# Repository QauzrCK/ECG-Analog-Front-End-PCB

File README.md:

# ECG-Analog-Front-End-PCB

# Low-Noise ECG Biopotential Analog Front-End (AFE)

A single-supply ($3.3\text{ V}$) analog front-end designed to extract, filter, and amplify $1\text{ mV}_{\text{pp}}$ electrocardiography (ECG) signals for microcontroller ADC acquisition, verified in **LTspice** and laid out as a 2-layer PCB in **KiCad**.

## System Specifications & Simulated Performance
* **Supply Voltage:** $3.3\text{ V}$ single-supply ($V_{\text{ref}} = 1.65\text{ V}$ mid-rail bias)
* **Mid-Band Gain:** $530.9\text{ V/V}$ ($54.5\text{ dB}$)
* **Passband Bandwidth:** $3.39\text{ Hz} – 148.7\text{ Hz}$
* **Mains Interference Rejection:** $>35\text{ dB}$ attenuation at $50\text{ Hz}$
* **Input-Referred Noise:** $<10\ \mu\text{V}_{\text{rms}}$ ($0.5–150\text{ Hz}$)

## Signal Chain Architecture
1. **Instrumentation Amplifier (`AD8226`):** Differential gain set to $G_1 = 1 + \frac{49.4\text{ k}\Omega}{5.6\text{ k}\Omega} = 9.82\text{ V/V}$, level-shifted to $V_{\text{ref}} = 1.65\text{ V}$ to prevent clipping from $\pm 150\text{ mV}$ electrode DC offsets.
2. **1st-Order High-Pass Filter:** $C_1 = 10\ \mu\text{F}$ and $R_2 = 4.7\text{ k}\Omega$ ($f_c = 3.39\text{ Hz}$) referenced to $V_{\text{ref}}$ to eliminate respiratory baseline wander while maintaining low source impedance into the notch stage.
3. **Active Twin-T $50\text{ Hz}$ Notch Filter (`LT1490`):** Symmetrical R-R-C / C-C-R bridge ($R = 31.6\text{ k}\Omega$, $C = 100\text{ nF}$, $f_0 = 50.37\text{ Hz}$) with unity-gain output bootstrapping to narrow the notch bandwidth and preserve QRS complex sharpness.
4. **2nd-Order Butterworth Sallen-Key Low-Pass & Final Gain (`LT1490`):** Equal-component low-pass stage ($R = 10.7\text{ k}\Omega$, $C = 100\text{ nF}$, $f_c = 148.7\text{ Hz}$, $A_v = 1.59\text{ V/V}$, $Q = 0.709$) cascaded into a non-inverting gain stage ($R_{10} = 33\text{ k}\Omega$, $R_{11} = 1\text{ k}\Omega$, $G_4 = 34\text{ V/V}$).

## PCB Layout Highlights (KiCad)
* **2-Layer Stackup:** Signal and power routing on top layer (`F.Cu`) with a continuous solid `GND` copper pour on the bottom layer (`B.Cu`) stitched via ground vias.
* **Component Selection:** 0805 SMD passives and SOIC-8 IC packages for hand-assembly and probing.

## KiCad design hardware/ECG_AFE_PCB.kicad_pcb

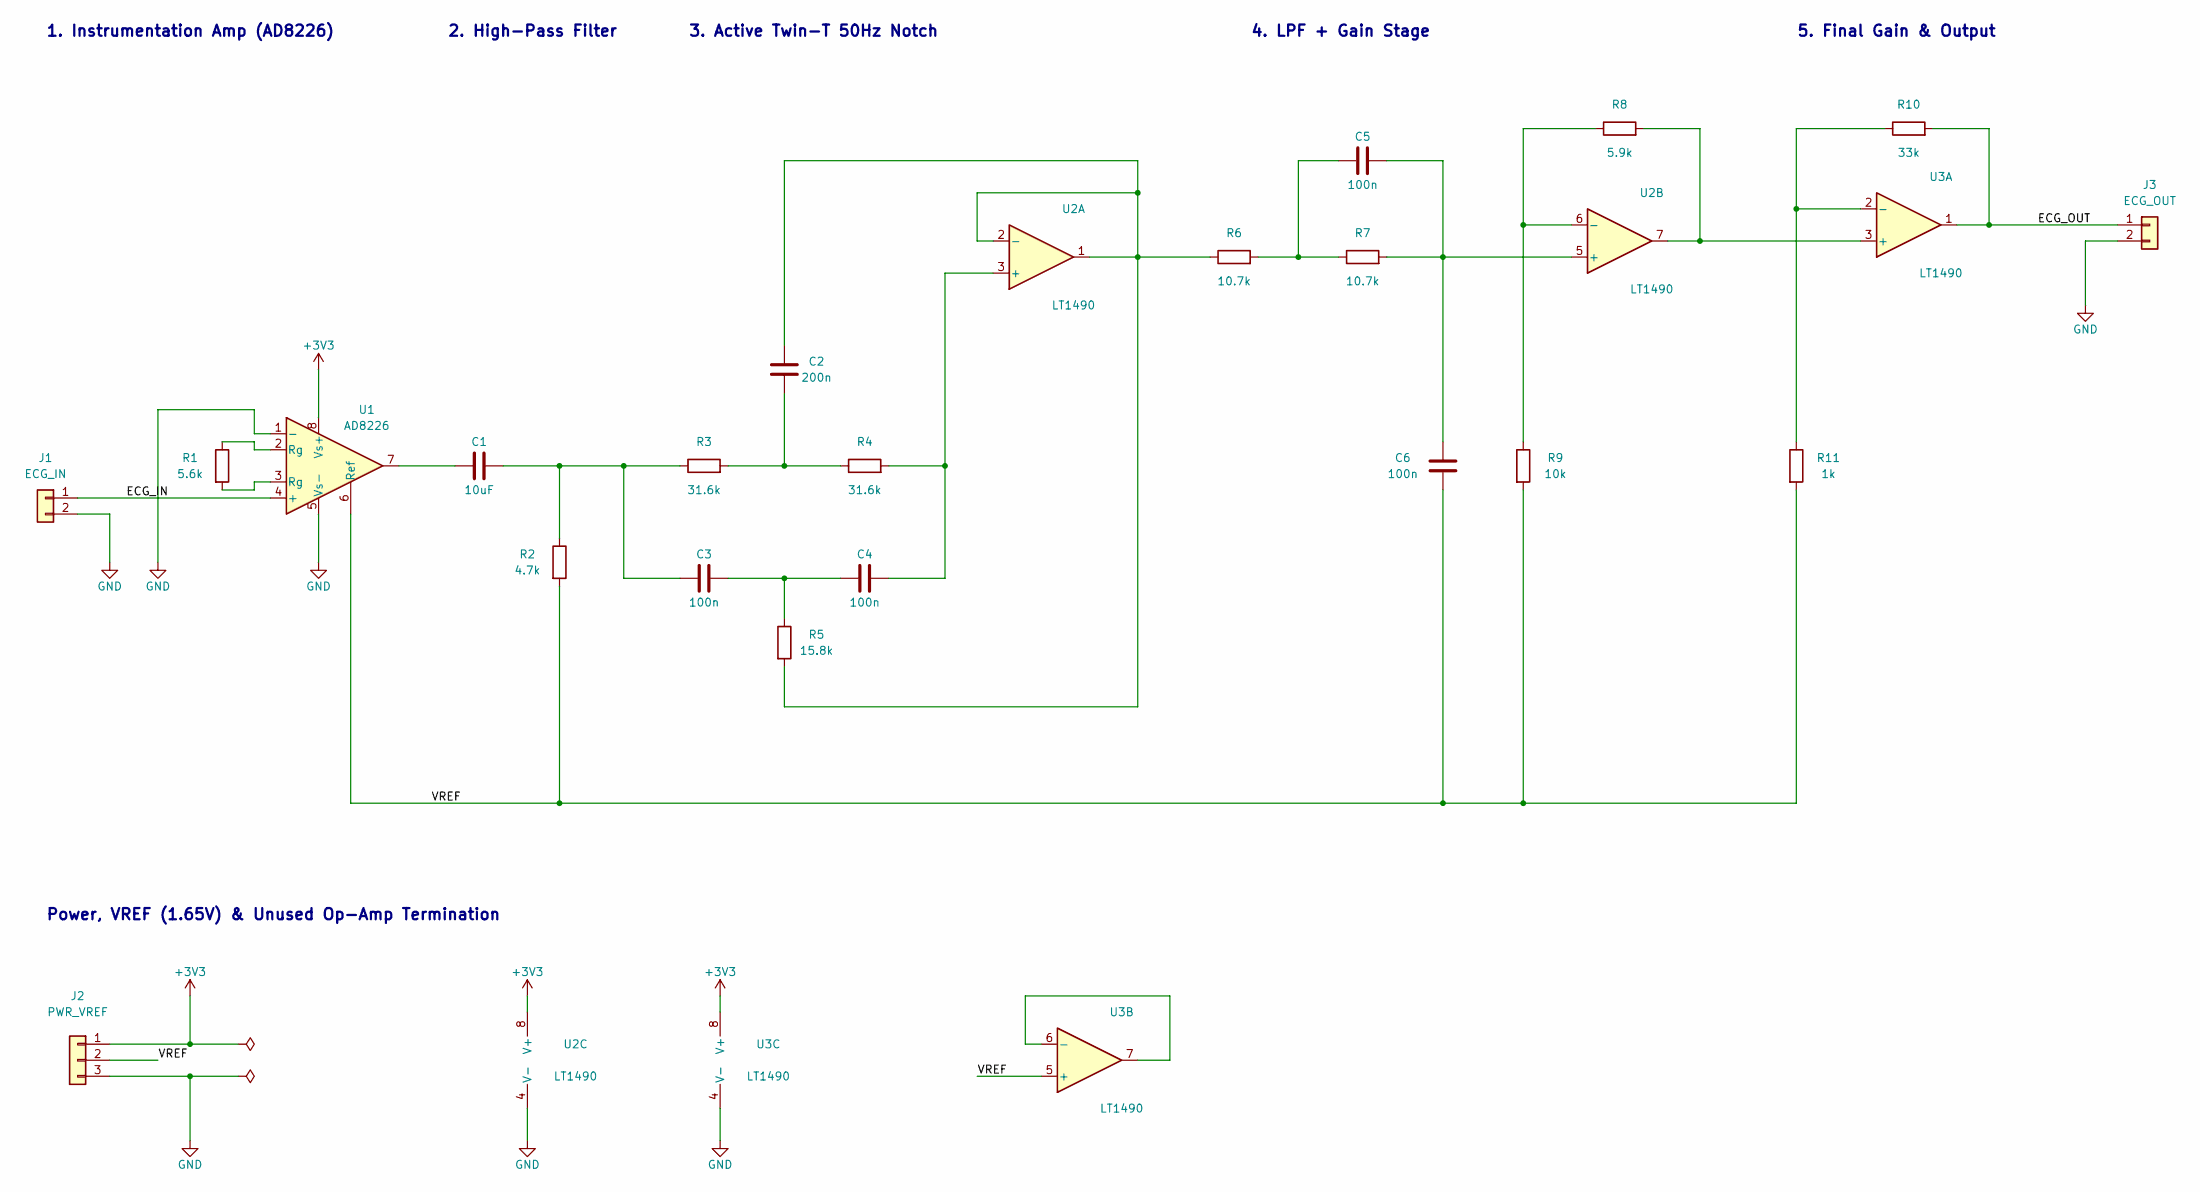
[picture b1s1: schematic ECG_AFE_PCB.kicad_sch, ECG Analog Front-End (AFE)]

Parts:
C1: 10uF; C_0805_2012Metric
C2: 200n; C_0805_2012Metric
C3, C4, C5, C6: 100n; C_0805_2012Metric
J1: ECG_IN; PinHeader_1x02_P2.54mm_Vertical
J2: PWR_VREF; PinHeader_1x03_P2.54mm_Vertical
J3: ECG_OUT; PinHeader_1x02_P2.54mm_Vertical
R1: 5.6k; R_0805_2012Metric
R2: 4.7k; R_0805_2012Metric
R3, R4: 31.6k; R_0805_2012Metric
R5: 15.8k; R_0805_2012Metric
R6, R7: 10.7k; R_0805_2012Metric
R8: 5.9k; R_0805_2012Metric
R9: 10k; R_0805_2012Metric
R10: 33k; R_0805_2012Metric
R11: 1k; R_0805_2012Metric
U1: AD8226; SOIC-8_3.9x4.9mm_P1.27mm
U2, U3: LT1490; SOIC-8_3.9x4.9mm_P1.27mm

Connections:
+3V3: J2.1, U1.8 (Vs+), U2.8 (V+), U3.8 (V+)
/ECG_IN: J1.1, U1.4 (+)
/ECG_OUT: J3.1, R10.2, U3.1
/VREF: C6.2, J2.2, R2.2, R9.2, R11.2, U1.6 (Ref), U3.5 (+)
GND: J1.2, J2.3, J3.2, U1.1 (-), U1.5 (Vs-), U2.4 (V-), U3.4 (V-)
unnamed: C1.1, U1.7
unnamed: C1.2, C3.1, R2.1, R3.1
unnamed: C2.2, R3.2, R4.1
unnamed: C3.2, C4.1, R5.1
unnamed: C5.1, R6.2, R7.1
unnamed: R1.1, U1.2 (Rg)
unnamed: R1.2, U1.3 (Rg)
unnamed: C4.2, R4.2, U2.3 (+)
unnamed: C2.1, R5.2, R6.1, U2.1, U2.2 (-)
unnamed: C5.2, C6.1, R7.2, U2.5 (+)
unnamed: R8.1, R9.1, U2.6 (-)
unnamed: R8.2, U2.7, U3.3 (+)
unnamed: R10.1, R11.1, U3.2 (-)
unnamed: U3.6 (-), U3.7

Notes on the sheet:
1. Instrumentation Amp (AD8226)
Power, VREF (1.65V) & Unused Op-Amp Termination
3. Active Twin-T 50Hz Notch
5. Final Gain & Output
4. LPF + Gain Stage
2. High-Pass Filter

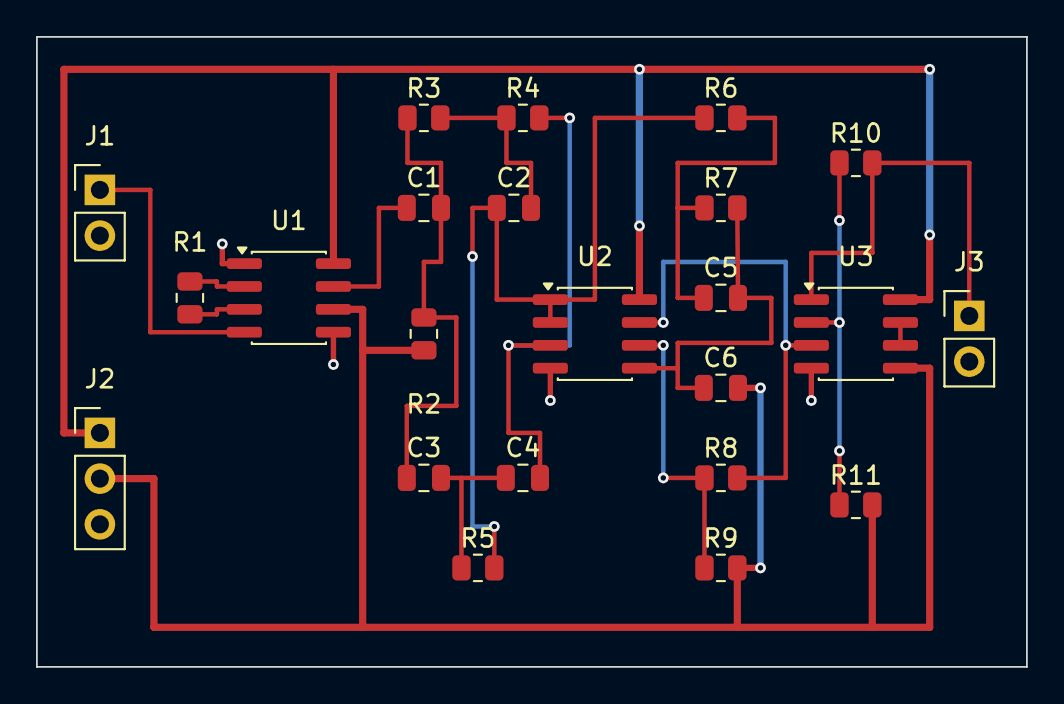
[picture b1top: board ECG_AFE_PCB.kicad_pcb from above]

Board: 2 copper layers, 55.0 x 35.0 mm, 23 parts (0 on the bottom side), 19 nets.
